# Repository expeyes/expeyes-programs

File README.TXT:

This directory contains all the expEYES programs and libraries - version 3.0  

BUILDING FROM THE SOURCE
========================

To build the package from the source, here are the required dependencies:
- python2.7
- lyx
- texlive binaries, fonts and packages
- image-magick
- gcc-avr and its utilities

To build and install the package, unfold the archive in some directory
and type the following commands:

  make; make install; sh postinst

TO RUN THE PROGRAMS
===================

You need to install the following modules and their dependences.

- python-imaging-tk
- tix
- python-tk
- python-scipy
- xmgrace
- python-pygrace
- python-serial
- python-usb
- udev

To start the expEYES main program:

$ expeyes

For expEYES Junior:

$ expeyes-junior

Each of the commands expeyes and expeyes-junior has its own manpage.

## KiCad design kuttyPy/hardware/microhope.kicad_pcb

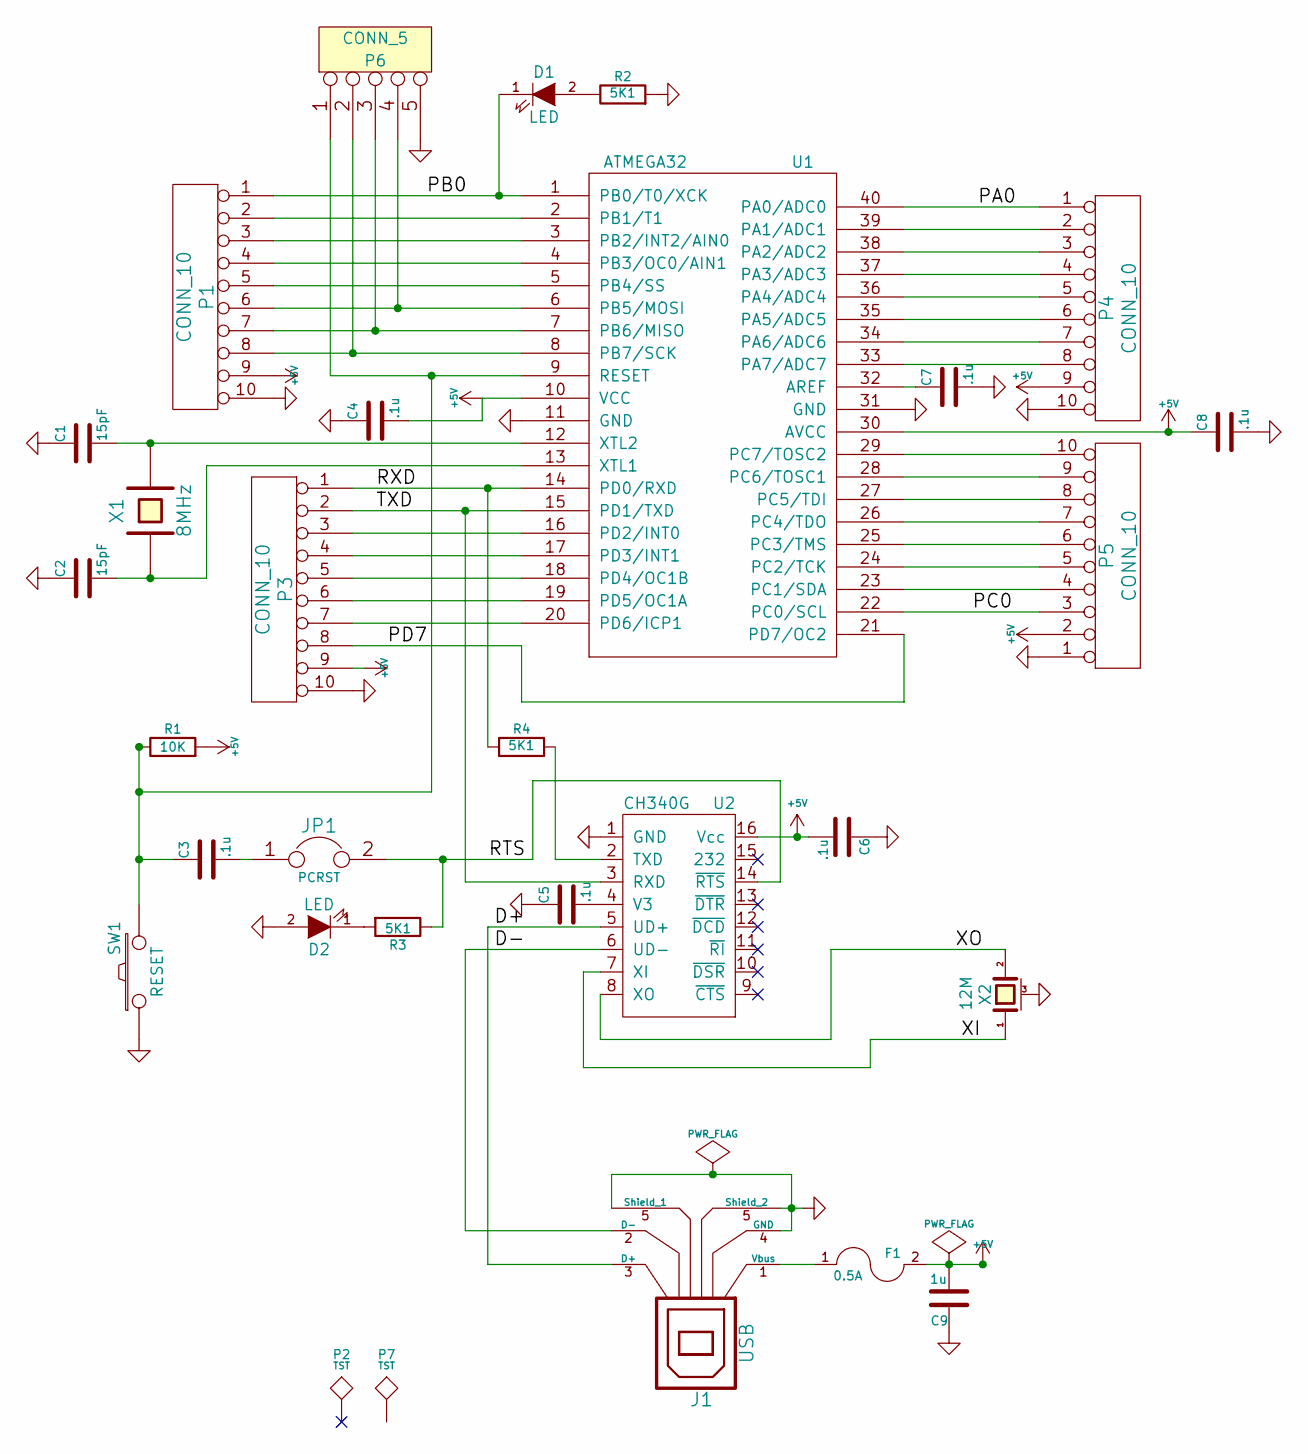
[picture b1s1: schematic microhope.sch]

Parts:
C1, C2: 15pF; C_0805
C3, C4, C5, C6, C7, C8: .1u; C_0805
C9: 1u; C_0805
D1, D2: LED; C_0805
F1: 0.5A; Fuse-1206-1812
J1: USB; USB_Micro-B-THsupport-2
JP1: PCRST; myPin_Header_Straight_1x02
P1, P3, P4, P5: CONN_10; Pin_Header_Straight_1x10-oval
P2, P7: TST; MountingHole-3mm
P6: CONN_5; myPin_Header_Straight_1x05
R1: 10K; R_0805
R2, R3, R4: 5K1; R_0805
SW1: RESET; myPin_Header_Straight_1x02
U1: ATMEGA32; DIP-40__600
U2: CH340G; SOIC-16_3.9x9.9mm_Pitch1.27mm
X1: 8MHz; Crystal_HC49-U_Vertical
X2: 12M; xtl-3225-3pin

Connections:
+5V: C4.2, C6.2, C8.1, C9.2, F1.2, P1.9, P3.9, P4.9, P5.2, R1.2, U1.10 (VCC), U1.30 (AVCC), U2.16 (Vcc)
/D+: J1.3 (D+), U2.5 (UD+)
/D-: J1.2 (D-), U2.6 (UD-)
/PA0: P4.1, U1.40 (PA0/ADC0)
/PB0: D1.1 (K), P1.1, U1.1 (PB0/T0/XCK)
/PC0: P5.3, U1.22 (PC0/SCL)
/PD7: P3.8, U1.21 (PD7/OC2)
/RTS: JP1.2, R3.1, U2.14 (~RTS)
/RXD: P3.1, R4.1, U1.14 (PD0/RXD)
/TXD: P3.2, U1.15 (PD1/TXD), U2.3 (RXD)
/XI: U2.7 (XI), X2.1
/XO: U2.8 (XO), X2.2
GND: C1.1, C2.1, C4.1, C5.1, C6.1, C7.2, C8.2, C9.1, D2.2 (A), J1.4 (GND), J1.5 (Shield_1), P1.10, P3.10, P4.10, P5.1, P6.5, R2.2, SW1.1, U1.11 (GND), U1.31 (GND), U2.1 (GND), X2.3 (case)
unnamed: C1.2, U1.12 (XTL2), X1.2
unnamed: C2.2, U1.13 (XTL1), X1.1
unnamed: C3.1, P6.1, R1.1, SW1.2, U1.9 (RESET)
unnamed: C3.2, JP1.1
unnamed: C5.2, U2.4 (V3)
unnamed: C7.1, U1.32 (AREF)
unnamed: D1.2 (A), R2.1
unnamed: D2.1 (K), R3.2
unnamed: F1.1, J1.1 (Vbus)
unnamed: P1.2, U1.2 (PB1/T1)
unnamed: P1.3, U1.3 (PB2/INT2/AIN0)
unnamed: P1.4, U1.4 (PB3/OC0/AIN1)
unnamed: P1.5, U1.5 (PB4/SS)
unnamed: P1.6, P6.4, U1.6 (PB5/MOSI)
unnamed: P1.7, P6.3, U1.7 (PB6/MISO)
unnamed: P1.8, P6.2, U1.8 (PB7/SCK)
unnamed: P3.3, U1.16 (PD2/INT0)
unnamed: P3.4, U1.17 (PD3/INT1)
unnamed: P3.5, U1.18 (PD4/OC1B)
unnamed: P3.6, U1.19 (PD5/OC1A)
unnamed: P3.7, U1.20 (PD6/ICP1)
unnamed: P4.2, U1.39 (PA1/ADC1)
unnamed: P4.3, U1.38 (PA2/ADC2)
unnamed: P4.4, U1.37 (PA3/ADC3)
unnamed: P4.5, U1.36 (PA4/ADC4)
unnamed: P4.6, U1.35 (PA5/ADC5)
unnamed: P4.7, U1.34 (PA6/ADC6)
unnamed: P4.8, U1.33 (PA7/ADC7)
unnamed: P5.4, U1.23 (PC1/SDA)
unnamed: P5.5, U1.24 (PC2/TCK)
unnamed: P5.6, U1.25 (PC3/TMS)
unnamed: P5.7, U1.26 (PC4/TDO)
unnamed: P5.8, U1.27 (PC5/TDI)
unnamed: P5.9, U1.28 (PC6/TOSC1)
unnamed: P5.10, U1.29 (PC7/TOSC2)
unnamed: R4.2, U2.2 (TXD)

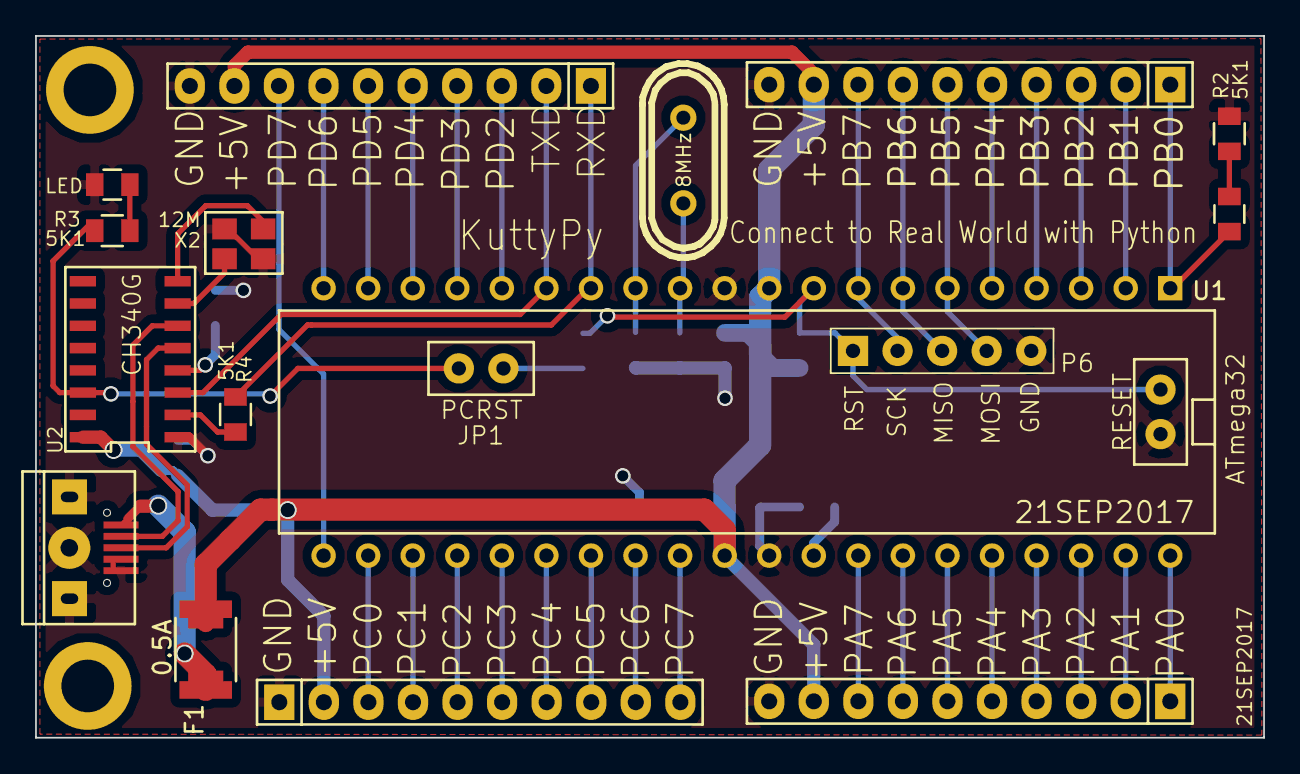
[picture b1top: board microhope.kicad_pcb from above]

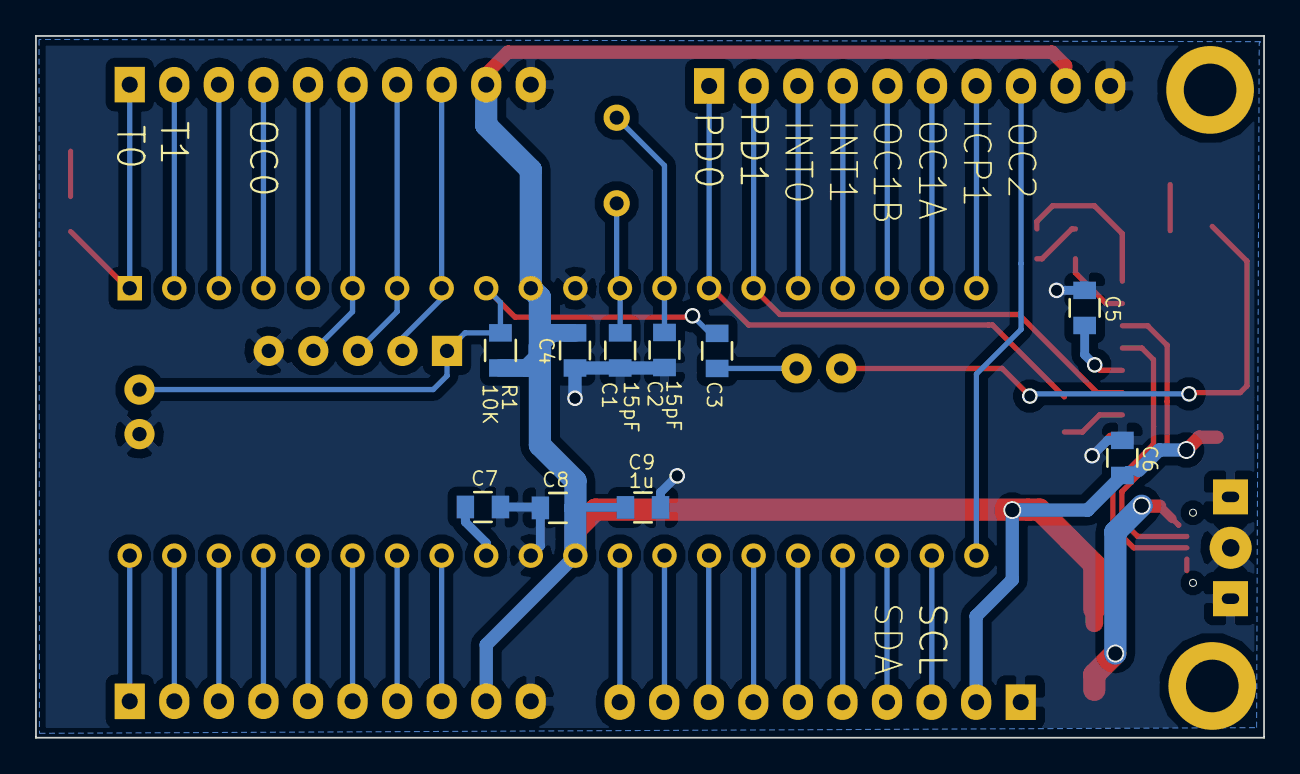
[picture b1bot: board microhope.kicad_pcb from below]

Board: 2 copper layers, 70.0 x 40.0 mm, 30 parts (10 on the bottom side), 49 nets.

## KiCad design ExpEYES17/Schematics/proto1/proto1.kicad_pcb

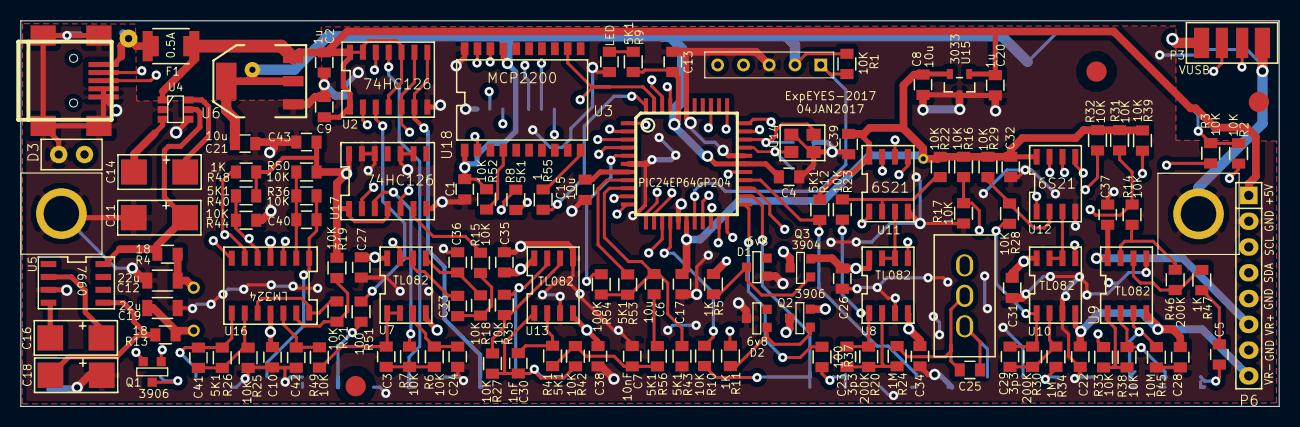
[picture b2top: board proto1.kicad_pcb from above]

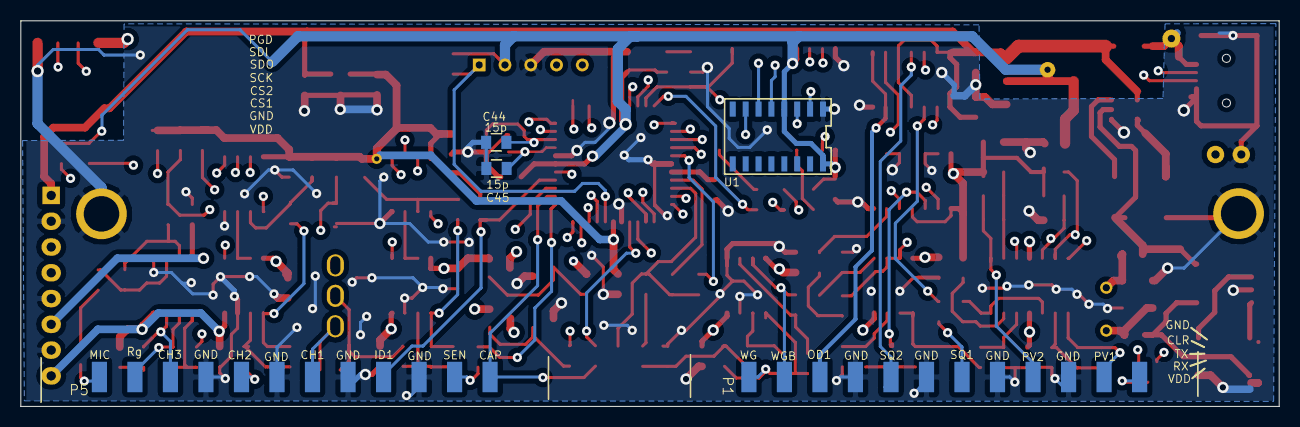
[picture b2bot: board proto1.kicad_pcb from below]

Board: 4 copper layers, 124.0 x 38.0 mm, 144 parts (5 on the bottom side), 102 nets.

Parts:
C1, C3, C4, C9, C10, C13, C17, C22, C24, C25, C26, C27, C28, C31, C32, C33, C34, C35, C36, C37, C38, C39, C40, C41, C42, C43: 0.1u; C_0805
C2, C5, C20: 1u; C_0805
C6, C8, C15, C21: 10u; C_0805
C7: 10nF; C_0805
C11, C14, C16, C18: 100u; TantalC_SizeC_EIA-6032_Reflow
C12, C19: 22u; C_1206
C23, C29: 3p3; C_0805
C30: 1nF; C_0805
C44, C45: 15p; C_0805
CON1: USB-MINI-B; myUSB_MINI_B
D1, D2: 6v8; SOT-23-zener
D3: LED; myPin_Header_Straight_1x02
D4: LED; C_0805
F1: 0.5A; Fuse-1206-1812
FM1, FM2, FM3: V-; fiducial
MH1, MH2: M; MountingHole-clear
P1: outputs; speaker-header-14-small
P2: prog; PICKIT-PROG
P3: USB2; my-4pin-smd
P5: Inputs; speaker-header-14-small
P6: exp; myPin_Header_Straight_1x08-oval
Q1, Q2: 3906; SOT-23-EBC
Q3: 3904; SOT-23-EBC
R1, R2, R3, R6, R7, R10, R14, R15, R16, R17, R18, R19, R21, R22, R23, R25, R27, R28, R29, R31, R32, R33, R35, R36, R38, R39, R42, R44, R49, R50, R52: 10K; R_0805
R4, R13: 18; R_0805
R5, R11, R47, R48: 1K; R_0805
R8, R9, R12, R26, R40, R41, R43, R53, R56: 5K1; R_0805
R20, R30, R46: 200K; R_0805
R24, R34: 1M; R_0805
R37, R51: 100; R_0805
R45: 10M; R_0805
R54: 100K; R_0805
R55: 1; R_0805
SW1: sw; mySwitch-3way
TP1: AVdd; myTestPoint
TP2: Vdd; myTestPoint
TP3: V+; myTestPoint
TP4: Vusb; myTestPoint
TP5: V-; myTestPoint
U1: CH340G; SOIC-16_3.9x9.9mm_Pitch1.27mm
U2, U17: 74HC126; SOIC-14_3.9x8.7mm_Pitch1.27mm
U3: PIC24EP64GP204; TQFP-44
U4: TC1240A; SOT-23-6
U5: 7660; SOIC-8_3.9x4.9mm_Pitch1.27mm
U6: LM1117-3.3; SOT-223
U7, U8, U9, U10, U13: TL082; SOIC-8_3.9x4.9mm_Pitch1.27mm
U11, U12: 6S21; SOIC-8_3.9x4.9mm_Pitch1.27mm
U14: XTL-4pin; xtl-3225
U15: 3033; sot23
U16: LM324; SOIC-14_3.9x8.7mm_Pitch1.27mm
U18: MCP2200; SOIC-20-W

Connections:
12MHz: C44.1, U1.7, U3.31, U14.3, U18.2
+5V: C2.2, C9.2, C20.2, F1.2, P6.1, U2.1, U2.4, U2.10, U2.13, U2.14, U4.1, U6.3, U15.1
/D+: CON1.3, P3.3, U1.5, U18.19
/D-: CON1.2, P3.2, U1.6, U18.18
/OD1: U2.5, U2.9, U3.2, U3.10
/PGC2: P2.5, U2.12, U3.42
/PGD2: P2.4, U3.41
/SQ1: U2.2, U3.1, U3.11
/SQ2: U3.3, U17.2
/SQ3: U3.4, U17.5
AN8: R8.2, U3.27
AVdd: C8.1, C17.2, C32.2, C39.2, C43.1, R12.1, R16.2, R19.1, R22.2, R29.1, R31.2, R32.2, R39.2, R40.1, R48.2, R50.1, TP1.1, U3.17, U11.8, U12.8, U15.2, U17.1, U17.4, U17.14
BOD1: P1.10, U2.6, U2.8
CAP: P5.12, R10.2, U3.24
CCS: P1.1, Q1.3, U3.25
CH1: C25.2, P5.7, SW1.3
CH1out: U3.22, U11.1
CH2: P5.5, R34.1
CH2out: U3.19, U12.1
CH3: P5.3, R45.2, U9.3
CH3out: R32.1, R33.1, U3.20
CS.CH1: U3.12, U11.5
CS.CH2: U3.13, U12.5
GND: C1.1, C2.1, C4.2, C7.2, C8.2, C9.1, C10.2, C11.2, C12.2, C13.1, C15.2, C17.1, C18.1, C19.1, C20.1, C21.2, C22.1, C24.2, C26.1, C27.1, C28.1, C31.1, C32.1, C34.1, C35.1, C36.2, C37.1, C38.1, C39.1, C42.2, C43.2, C44.2, C45.2, CON1.4, CON1.5, CON1.6, CON1.7, CON1.8, CON1.9, D1.1, D2.2, D3.1, D4.1, MH1.1, MH2.1, P1.3, P1.5, P1.7, P1.9, P2.3, P3.4, P5.4, P5.6, P5.8, P5.10, P6.2, P6.5, P6.7, R17.2, R25.1, R43.2, R44.2, R45.1, U1.1, U2.7, U3.6, U3.16, U3.29, U3.39, U4.2, U4.4, U5.3, U6.1, U8.3, U9.5, U10.3, U11.4, U12.4, U13.3, U13.5, U14.2, U14.4, U15.3, U17.7, U17.9, U17.10, U17.12, U17.13, U18.20
ID1: P5.11, R37.1
MCLR: P2.1, R1.2, U3.18
MIC: C5.2, P5.1, R39.1
MICout: R14.1, R31.1, U3.21
unnamed: C3.1, R6.2, R7.1
unnamed: C3.2, R49.1, U7.1, U7.2
unnamed: C5.1, R47.2
unnamed: C6.2, R56.1
unnamed: C7.1, R41.2, R42.1, R56.2
unnamed: C11.1, R4.2, U4.5, U5.8
unnamed: C14.1, U4.6
unnamed: C14.2, U4.3
unnamed: C15.1, U3.7
unnamed: C16.1, U5.2
unnamed: C16.2, U5.4
unnamed: C18.2, R13.2, U5.5
unnamed: C23.1, R20.1, R23.2, U8.1
unnamed: C23.2, R20.2, R24.2, U8.2
unnamed: C24.1, R6.1, U7.3
unnamed: C25.1, R24.1, SW1.2
unnamed: C29.1, R28.1, R30.1, U10.1
unnamed: C29.2, R30.2, R34.2, U10.2
unnamed: C30.2, R41.1, U13.2
unnamed: C33.1, R15.1, R18.2
unnamed: C36.1, R18.1, U7.5
unnamed: C40.2, R36.1, R50.2, U16.2
unnamed: C41.1, R25.2, R26.1, U16.9
unnamed: C42.1, R49.2, U16.12
unnamed: C45.1, U3.30, U14.1
unnamed: D1.2, Q3.2, R5.2
unnamed: D2.1, Q2.2, R11.2
unnamed: D3.2, R8.1
unnamed: D4.2, R9.1
unnamed: Q1.1, R48.1, U16.6
unnamed: Q1.2, U16.7
unnamed: R7.2, U17.3
unnamed: R14.2, R46.2, U9.7
unnamed: R15.2, U17.6
unnamed: R16.1, R17.1, U8.5, U10.5
unnamed: R19.2, R21.1, U16.13
unnamed: R21.2, U16.10, U16.14
unnamed: R22.1, R23.1, U11.2
unnamed: R27.2, R35.1, U13.6
unnamed: R28.2, R29.2, U12.2
unnamed: R33.2, R38.2, U9.1
unnamed: R37.2, U3.23
unnamed: R46.1, R47.1, U9.6
unnamed: R51.1, U2.3
unnamed: R52.1, U18.4
unnamed: R55.1, U18.10
unnamed: U10.6, U10.7, U12.3
unnamed: U8.6, U8.7, U11.3
PDC2: C33.2, U7.6, U7.7, U16.3
PV1: C41.2, P1.2, R26.2, U16.8
PV2: C40.1, P1.4, R36.2, U16.1
RB14: R40.2, R44.1, U3.14, U16.5
RB15: R10.1, U3.15
RXD: U1.3, U3.43, U18.12
Rg: P5.2, R38.1, U9.2
SCK: U3.36, U11.7, U12.7
SCL: P6.3, R2.1, U3.33
SDA: P6.4, R3.1, U3.32
SDO: U3.34, U11.6, U12.6
SEN: P5.9, R12.2, U3.26
SQ4: R54.1, U3.5
SQ4A: R53.1, U3.8
SQ4B: C6.1, R43.1, R53.2, R54.2, U3.9
SQR1: P1.6, R51.2
SQR2: P1.8, U2.11
TXD: R55.2, U1.2, U3.44
V+: C12.1, C27.2, C35.2, Q3.3, R4.1, R5.1, TP3.1, U7.8, U13.8, U16.4
V-: C10.1, C19.2, C38.2, Q2.3, R11.1, R13.1, TP5.1, U7.4, U13.4, U16.11
VR+: C26.2, C31.2, C37.2, P6.6, Q3.1, U8.8, U9.8, U10.8
VR-: C22.2, C28.2, C34.2, P6.8, Q2.1, U8.4, U9.4, U10.4
VUSB: CON1.1, F1.1, P3.1, TP4.1
Vdd: C1.2, C4.1, C13.2, C21.1, P2.2, R1.1, R2.2, R3.2, R9.2, R52.2, TP2.1, U1.4, U1.16, U3.28, U3.40, U6.2, U6.4, U18.1, U18.17
WG1: C30.1, P1.12, R27.1, R42.2, U13.1
WG2: P1.11, R35.2, U13.7

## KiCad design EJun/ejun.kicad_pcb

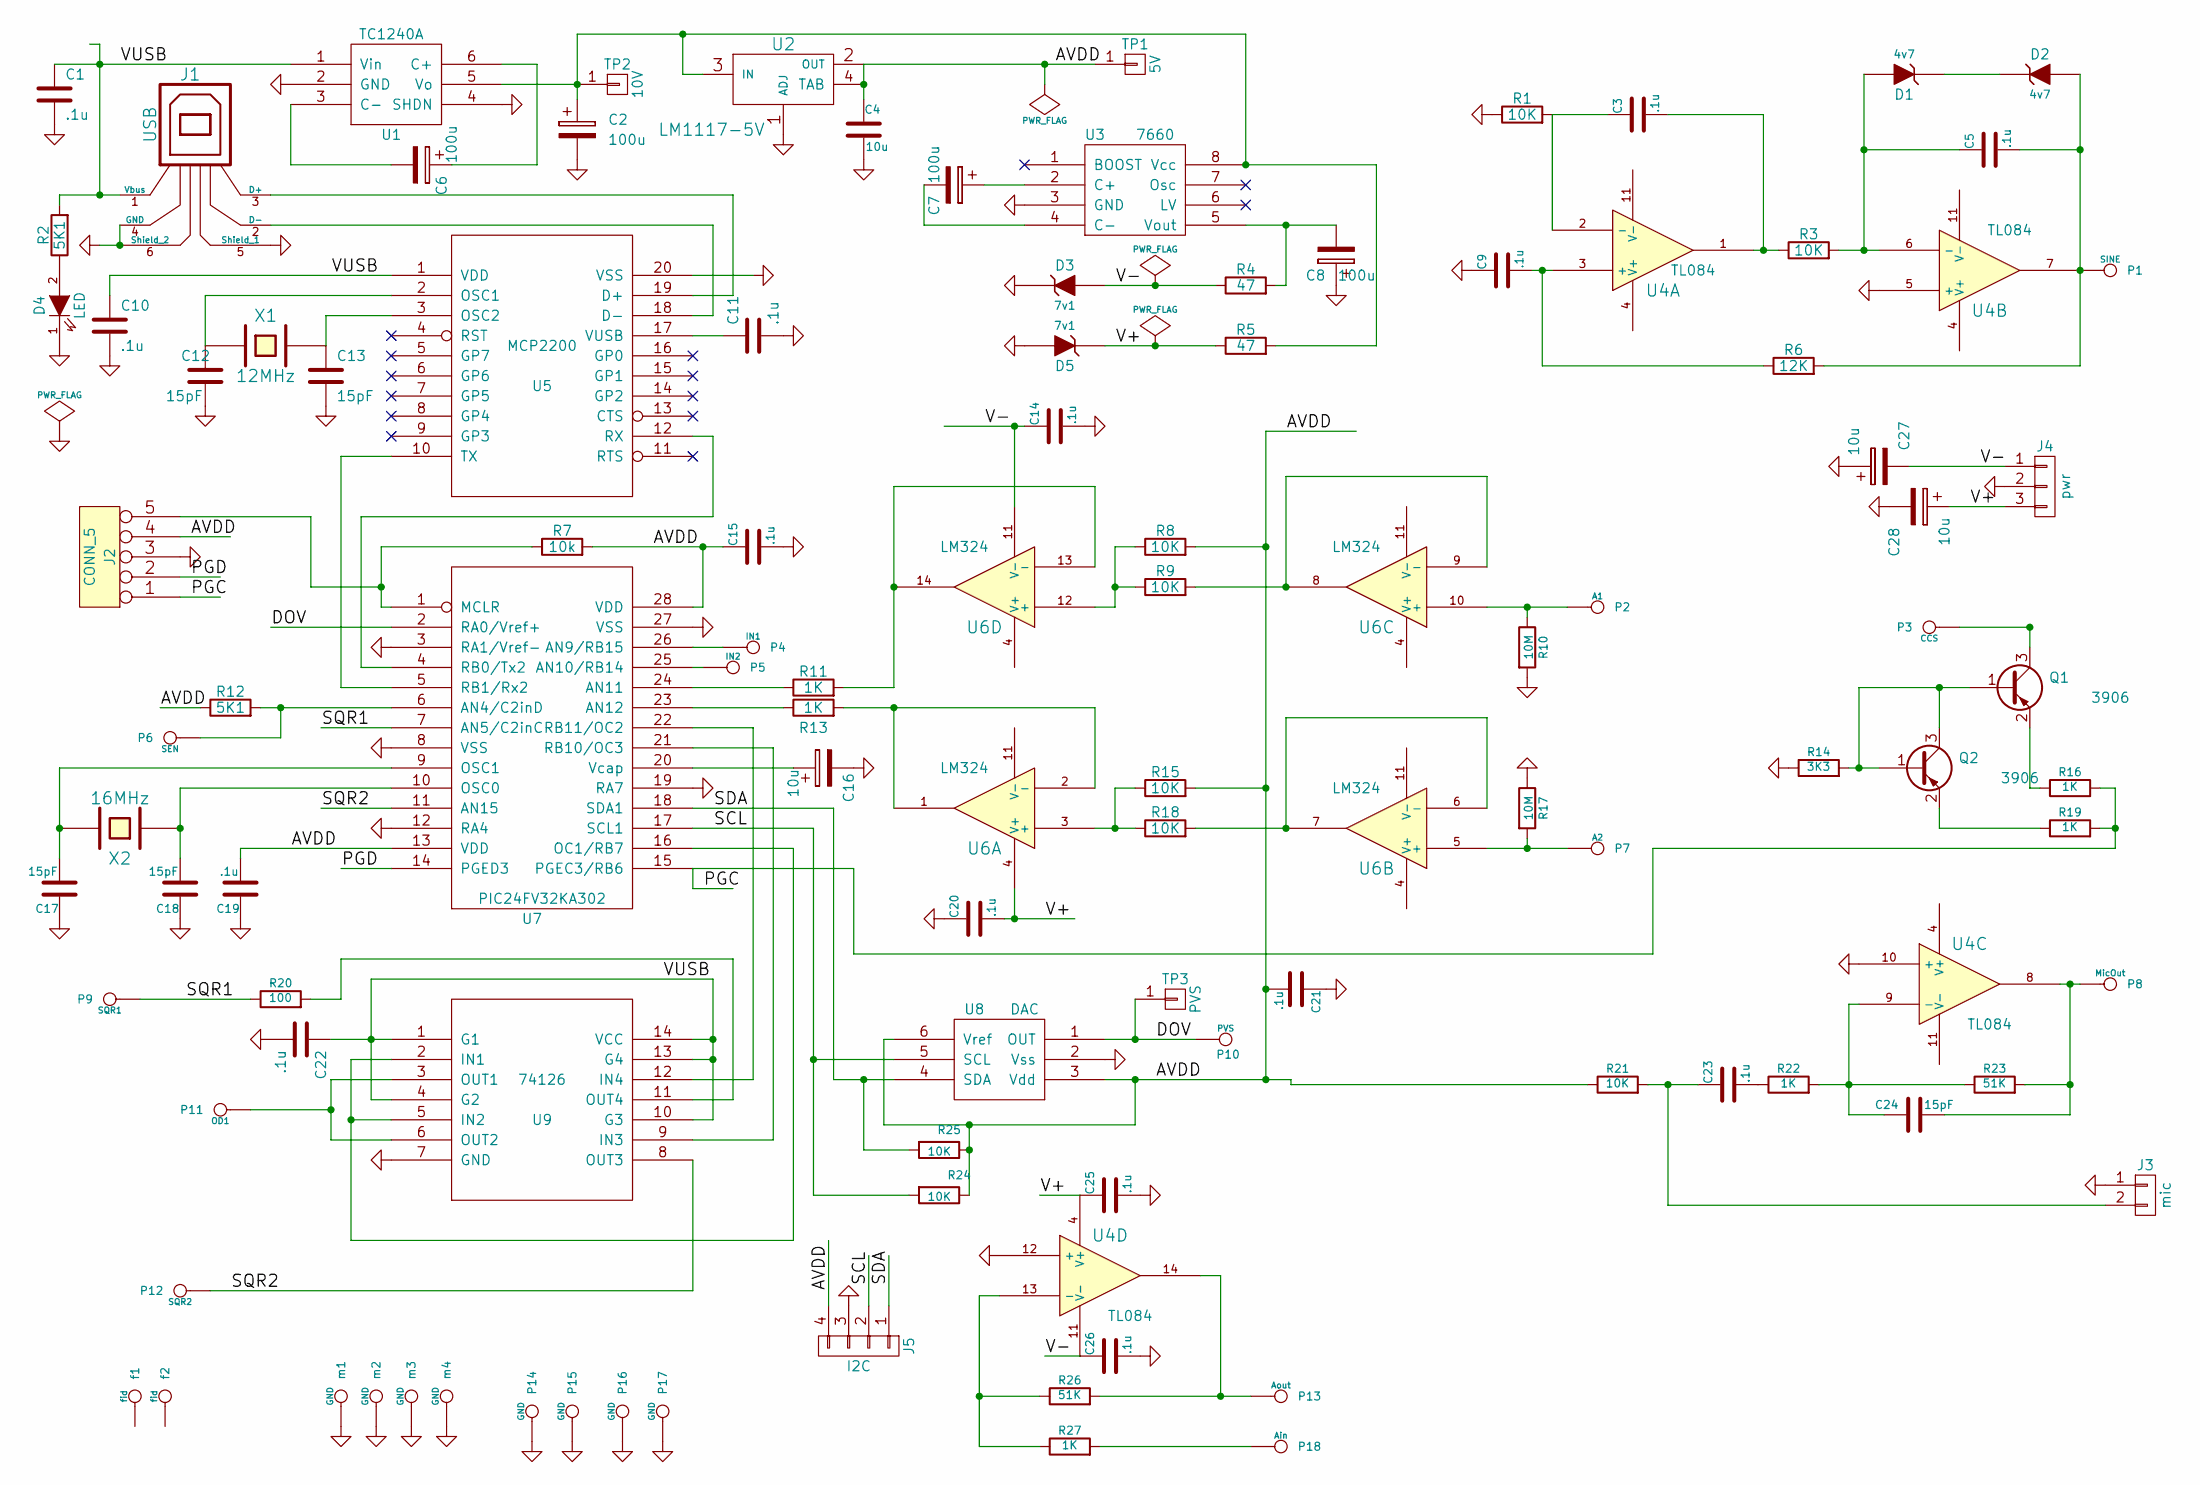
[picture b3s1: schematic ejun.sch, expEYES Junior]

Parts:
C1, C3, C5, C9, C10, C11, C14, C15, C19, C20, C21, C22, C23, C25, C26: .1u; C_0805-0.1uf
C2, C6, C7, C8: 100u; TantalC_SizeC_EIA-6032_Reflow
C4, C16, C27, C28: 10u; myTantalC_SizeA
C12, C13, C17, C18: 15pF; C_0805
C24: 15pF; C_0805-0.1uf
D1, D2: 4v7; zener
D3, D5: 7v1; zener
D4: LED; myPin_Header_Straight_1x02
J1: USB; USB_A-new
J2: CONN_5; PICKIT-PROG
J3: mic; myPin_Header_Straight_1x02
J4: pwr; mySocket_3x1
J5: I2C; myPin_Header_Straight_1x04
P1: SINE; myPhoenixCon-new
P2: A1; myPhoenixCon-new
P3: CCS; myPhoenixCon-new
P4: IN1; myPhoenixCon-new
P5: IN2; myPhoenixCon-new
P6: SEN; myPhoenixCon-new
P7: A2; myPhoenixCon-new
P8: MicOut; myPhoenixCon-new
P9: SQR1; myPhoenixCon-new
P10: PVS; myPhoenixCon-new
P11: OD1; myPhoenixCon-new
P12: SQR2; myPhoenixCon-new
P13: Aout; myPhoenixCon-new
P14, P15, P16, P17: GND; myPhoenixCon-new
P18: Ain; myPhoenixCon-new
Q1, Q2: 3906; SOT-23-BEC
R1, R3, R8, R9, R15, R18, R21, R24, R25: 10K; C_0805
R2, R12: 5K1; C_0805
R4, R5: 47; C_1206
R6: 12K; C_0805
R7: 10k; C_0805
R10, R17: 10M; C_0805
R11, R13, R16, R19, R22, R27: 1K; C_0805
R14: 3K3; C_0805
R20: 100; C_0805
R23, R26: 51K; C_0805
TP1: 5V; myTestPoint
TP2: 10V; myTestPoint
TP3: PVS; myTestPoint
U1: TC1240A; SOT-23-6
U2: LM1117-5V; SOT-223
U3: 7660; SOIC-8_3.9x4.9mm_Pitch1.27mm
U4: TL084; SOIC-14_3.9x8.7mm_Pitch1.27mm
U5: MCP2200; SOIC-20-W
U6: LM324; SOIC-14_3.9x8.7mm_Pitch1.27mm
U7: PIC24FV32KA302; SOIC-28-W
U8: DAC; SOT-23-6
U9: 74126; SOIC-14_3.9x8.7mm_Pitch1.27mm
X1: 12MHz; Crystal_HC49-U_Vertical
X2: 16MHz; Crystal_HC49-U_Vertical
f1, f2: fid; fiducial
m1, m2, m3, m4: GND; 3mm-mounting-hole

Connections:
/AVDD: C4.1, C15.1, C19.2, C21.2, J2.4, J5.4, R7.2, R8.2, R12.1, R15.2, R21.1, R24.1, R25.1, TP1.1, U2.2 (OUT), U2.4 (TAB), U7.13 (VDD), U7.28 (VDD), U8.3 (Vdd), U8.6 (Vref)
/DOV: P10.1, TP3.1, U7.2 (RA0/Vref+), U8.1 (OUT)
/PGC: J2.1, R16.2, R19.2, U7.15 (PGEC3/RB6)
/PGD: J2.2, U7.14 (PGED3)
/SCL: J5.2, R24.2, U7.17 (SCL1), U8.5 (SCL)
/SDA: J5.1, R25.2, U7.18 (SDA1), U8.4 (SDA)
/SQR1: P9.1, R20.1, U7.7 (AN5/C2inC)
/SQR2: P12.1, U7.11 (AN15), U9.8 (OUT3)
/V+: C20.2, C25.1, C28.1, D5.1 (K), J4.3, R5.1, U4.4 (V+), U6.4 (V+)
/V-: C14.1, C26.1, C27.2, D3.2 (A), J4.1, R4.1, U4.11 (V-), U6.11 (V-)
/VUSB: C1.1, C10.1, C22.1, J1.1 (Vbus), R2.2, U1.1 (Vin), U5.1 (VDD), U9.1 (G1), U9.4 (G2), U9.10 (G3), U9.13 (G4), U9.14 (VCC)
GND: C1.2, C2.2, C4.2, C8.1, C9.1, C10.2, C11.2, C12.2, C13.2, C14.2, C15.2, C16.2, C17.1, C18.1, C19.1, C20.1, C21.1, C22.2, C25.2, C26.2, C27.1, C28.2, D3.1 (K), D4.1 (K), D5.2 (A), J1.4 (GND), J1.5 (Shield_1), J1.6 (Shield_2), J2.3, J3.1, J4.2, J5.3, P14.1, P15.1, P16.1, P17.1, R1.1, R10.2, R14.1, R17.1, U1.2 (GND), U1.4 (SHDN), U2.1 (ADJ), U3.3 (GND), U4.5 (+), U4.10 (+), U4.12 (+), U5.20 (VSS), U7.3 (RA1/Vref-), U7.8 (VSS), U7.12 (RA4), U7.19 (RA7), U7.27 (VSS), U8.2 (Vss), U9.7 (GND), m1.1, m2.1, m3.1, m4.1
unnamed: C2.1, R5.2, TP2.1, U1.5 (Vo), U2.3 (IN), U3.8 (Vcc)
unnamed: C3.1, R1.2, U4.2 (-)
unnamed: C3.2, R3.1, U4.1
unnamed: C5.1, D1.2 (A), R3.2, U4.6 (-)
unnamed: C5.2, D2.2 (A), P1.1, R6.2, U4.7
unnamed: C6.1, U1.6 (C+)
unnamed: C6.2, U1.3 (C-)
unnamed: C7.1, U3.2 (C+)
unnamed: C7.2, U3.4 (C-)
unnamed: C8.2, R4.2, U3.5 (Vout)
unnamed: C9.2, R6.1, U4.3 (+)
unnamed: C11.1, U5.17 (VUSB)
unnamed: C12.1, U5.2 (OSC1), X1.1
unnamed: C13.1, U5.3 (OSC2), X1.2
unnamed: C16.1, U7.20 (Vcap)
unnamed: C17.2, U7.9 (OSC1), X2.2
unnamed: C18.2, U7.10 (OSC0), X2.1
unnamed: C23.1, J3.2, R21.2
unnamed: C23.2, R22.1
unnamed: C24.1, R22.2, R23.1, U4.9 (-)
unnamed: C24.2, P8.1, R23.2, U4.8
unnamed: D1.1 (K), D2.1 (K)
unnamed: D4.2 (A), R2.1
unnamed: J1.2 (D-), U5.18 (D-)
unnamed: J1.3 (D+), U5.19 (D+)
unnamed: J2.5, R7.1, U7.1 (MCLR)
unnamed: P2.1, R10.1, U6.10 (+)
unnamed: P3.1, Q1.3 (C)
unnamed: P4.1, U7.26 (AN9/RB15)
unnamed: P5.1, U7.25 (AN10/RB14)
unnamed: P6.1, R12.2, U7.6 (AN4/C2inD)
unnamed: P7.1, R17.2, U6.5 (+)
unnamed: P11.1, U9.3 (OUT1), U9.6 (OUT2)
unnamed: P13.1, R26.2, U4.14
unnamed: P18.1, R27.2
unnamed: Q1.1 (B), Q2.1 (B), Q2.3 (C), R14.2
unnamed: Q1.2 (E), R16.1
unnamed: Q2.2 (E), R19.1
unnamed: R8.1, R9.1, U6.12 (+)
unnamed: R9.2, U6.8, U6.9 (-)
unnamed: R11.1, U7.24 (AN11)
unnamed: R11.2, U6.13 (-), U6.14
unnamed: R13.1, U7.23 (AN12)
unnamed: R13.2, U6.1, U6.2 (-)
unnamed: R15.1, R18.1, U6.3 (+)
unnamed: R18.2, U6.6 (-), U6.7
unnamed: R20.2, U9.11 (OUT4)
unnamed: R26.1, R27.1, U4.13 (-)
unnamed: U5.10 (TX), U7.5 (RB1/Rx2)
unnamed: U5.12 (RX), U7.4 (RB0/Tx2)
unnamed: U7.16 (OC1/RB7), U9.2 (IN1), U9.5 (IN2)
unnamed: U7.21 (RB10/OC3), U9.9 (IN3)
unnamed: U7.22 (RB11/OC2), U9.12 (IN4)

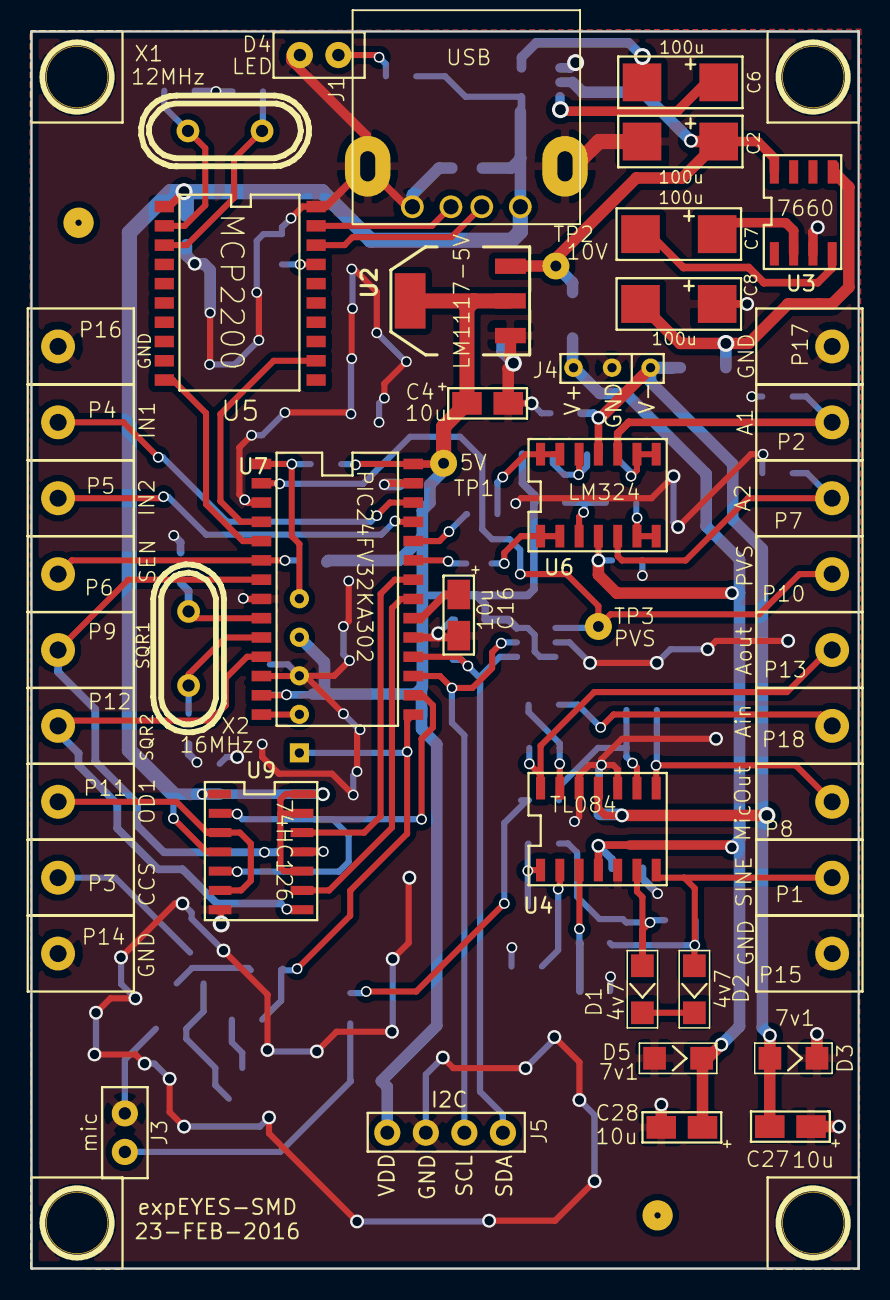
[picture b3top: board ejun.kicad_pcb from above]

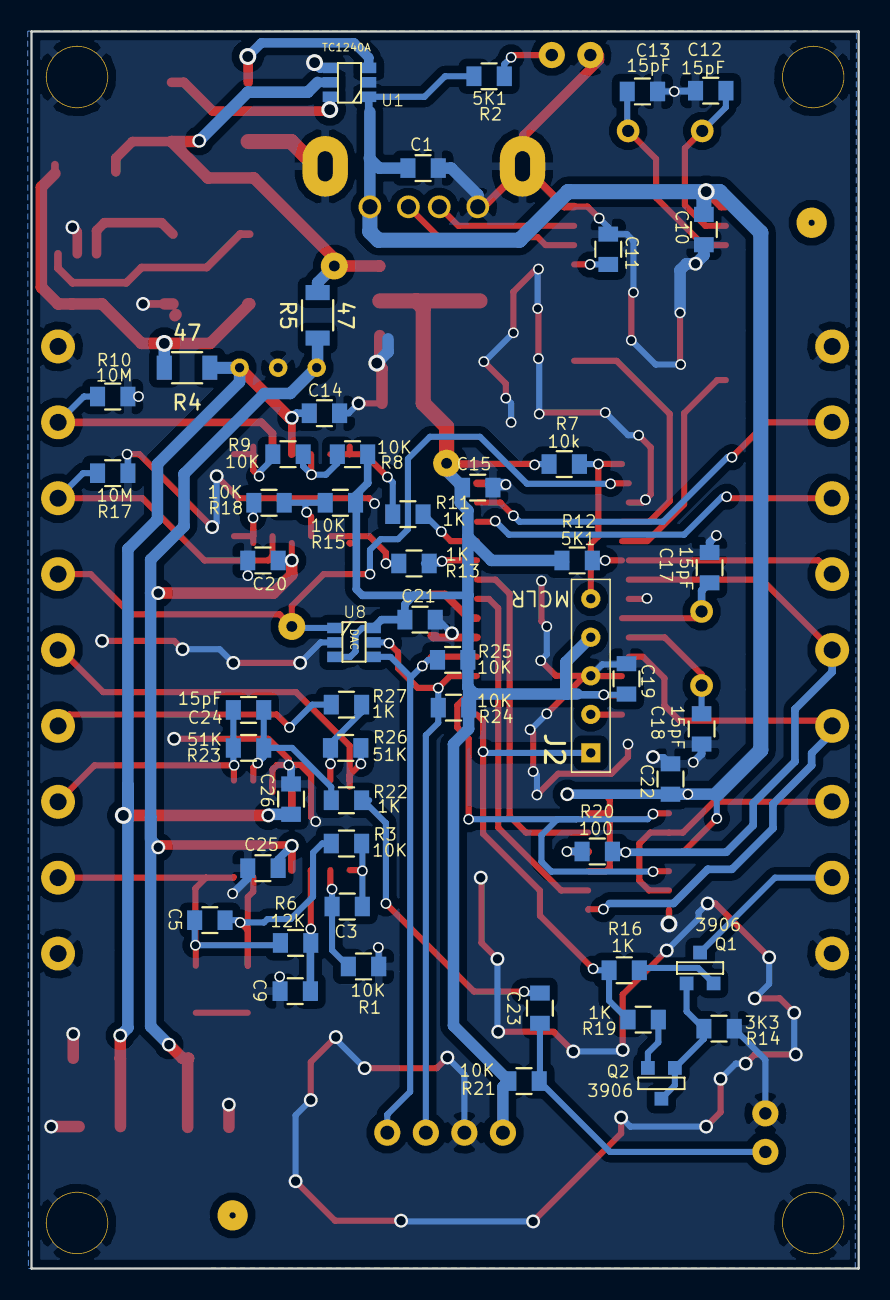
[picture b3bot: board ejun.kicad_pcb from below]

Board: 2 copper layers, 54.5 x 81.5 mm, 105 parts (52 on the bottom side), 65 nets.

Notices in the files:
EJun/ejun.kicad_pcb:
This is open Hardware, per the license CERN OHL
